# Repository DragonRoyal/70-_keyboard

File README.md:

# 70% keyboard

A low profile sleek 70% keyboard.

## Features
- **Hot Swappable**: Swap existing switches easily without needing to solder
- **LED**: Supports independently controlled RGB backlighting for each switch
- **Multi-Layered**: Work between multiple different layers for increased macros and switch options
- **TFT Screen**: A powerful and sharp TFT display 
- **Raspberry Pi**: Fast and dynamic microcontroller allowing for easy software customization
- **Rotary Encoder**: Easy to use knob for changing granular control such as volume, brightness etc

## CAD

## PCB 

> Firmware is coded in C using the QMK library

## BOM
|Type                         |Qty|Value                       |Exclude from BOM|Exclude from Board|Footprint                                                    |Price (with tax)|links                                                                                                                                                                                                                                                                                                                                                                                                                                                                                                                                            |
|-----------------------------|---|----------------------------|----------------|------------------|-------------------------------------------------------------|----------------|-------------------------------------------------------------------------------------------------------------------------------------------------------------------------------------------------------------------------------------------------------------------------------------------------------------------------------------------------------------------------------------------------------------------------------------------------------------------------------------------------------------------------------------------------|
|Microcontroller              |1  |RaspberryPi_Pico            |FALSE           |FALSE             |Module:RaspberryPi_Pico_Common_Unspecified                   |$4              | self-sourced                                                                                                                                                                                                                                                                                                                                                                                                                                                                                                                                    |
|Diode                        |79 |Diode 14B                   |FALSE           |FALSE             |Diode_SMD:D_SOD-123                                          |$15             | https://www.amazon.com/gp/product/B089KD46P6/ref=ox_sc_act_title_8?smid=A1K2H0ANPH97NN&psc=1                                                                                                                                                                                                                                                                                                                                                                                                                                                    |
|Led                          |78 |WS2812B                     |FALSE           |FALSE             |PCM_marbastlib-various:SK6812 Mini-E Leds                    |$6              | self-sourced                                                                                                                                                                                                                                                                                                                                                                                                                                                                                                                                    |
|Rotary Encoder               |1  |EC11 Rotary Encoder         |FALSE           |FALSE             |Rotary_Encoder:RotaryEncoder_Alps_EC11E-Switch_Vertical_H20mm|$3              | self sourced                                                                                                                                                                                                                                                                                                                                                                                                                                                                                                                                    |
|Switch                       |78 |Gateroen banana low profile |FALSE           |FALSE             |PCM_marbastlib-xp-gateron_lp:SW_KS33_HS_KS-2P02B01-02_HS_1u  |$35             | self sourced                                                                                                                                                                                                                                                                                                                                                                                                                                                                                                                                    |
|Screen                       |1  |1.47in TFT screen           |TRUE            |FALSE             |PCM_marbastlib-various:1.47IN TFT_SCREEN                     | 7              | self sourced                                                                                                                                                                                                                                                                                                                                                                                                                                                                                                                                    |
|Level Converter              |1  |3.3V 5V Level Shifter       |FALSE           |FALSE             |PCM_marbastlib-various:level_shifter                         |7               | self sourced                                                                                                                                                                                                                                                                                                                                                                                                                                                                                                                                    |
|3D printed parts (plate+case)|1  |PLA filament 500g           |TRUE            |FALSE             |None                                                         | 10             | self sourced                                                                                                                                                                                                                                                                                                                                                                                                                                                                                                                                    |
|Key Caps                     |78 |Key Cap set                 |TRUE            |TRUE              |NONE                                                         | 13             | https://www.amazon.com/GMKWTL-Keyboard-Compatiability-Mechanical-Keyboard/dp/B0DHZSBBGN/ref=sr_1_10?crid=Q8QKCUUYPY36&dib=eyJ2IjoiMSJ9.fwrs3L7kzoYC9Lyi1R3ookXQWckNlki_qPy9XYsRL8eoixaPVOBcJbsZt-iwJnTJds7WBFu0eCcz7btfrjkPINBELr45fnBbDHA4z57k4MjwkxalkegLYI5fEKua1gpFN4hqXenK0UHtjBB1nRiui-55GRccuGOSDW5j42Px5hd2BBhLpY2dmSPZnt28AmRuuPHAs3Wn1phLvo0gcR4tVQwwtv983OjqboYfD7py36w.qD3godhpSDs_aP7pM0q0AIdArKnzhV_a1bjScBHYfi8&dib_tag=se&keywords=keycaps%2Blow%2Bprofile&qid=1775969569&sprefix=keycaps%2Blow%2Bprofi%2Caps%2C273&sr=8-10&th=1|
|Hot Swap pieces              |78 |Pieces to enable hotswapping|FALSE           |FALSE             |None                                                         |$13             | https://www.amazon.com/DUROCK-Mechanical-Keyboard-Switches-Hot-Swap/dp/B0B4W9YMGM/ref=sr_1_2?crid=35CHQWRUJA015&dib=eyJ2IjoiMSJ9.JKoXkJJJrIVA4JnSSkGnStBHXR4IGGxla1AKDvP5V3XXNLep92NdhsBql2ii68qiNB_c7g-ZFRZQXi7_jpkLV9qVnHxPqgLZuBjQyTdpZ7GRyz4oyQSZOJoVgddlCynht3oA2-7a3M9IHi13k7zsOeL7wTkQXblP_iKm-qXsR8phlb-2kgSF3aj1uBRLhr7IE7VCK2ORV3m670alLx6cIYPoHnYoNUGfPmrVBh7ICmw.oYdHgUtbILh2GUhhMcQZcBHLQ_plr3crWkFkTJia-B8&dib_tag=se&keywords=hotswap&qid=1775969494&sprefix=hotswa%2Caps%2C238&sr=8-2                                           |
|PCB Board                    |1  |Pcb from JLCPCB             |FALSE           |FALSE             |                                                             |$35             | https://jlcpcb.com/                                                                                                                                                                                                                                                                                                                                                                                                                                                                                                                             |

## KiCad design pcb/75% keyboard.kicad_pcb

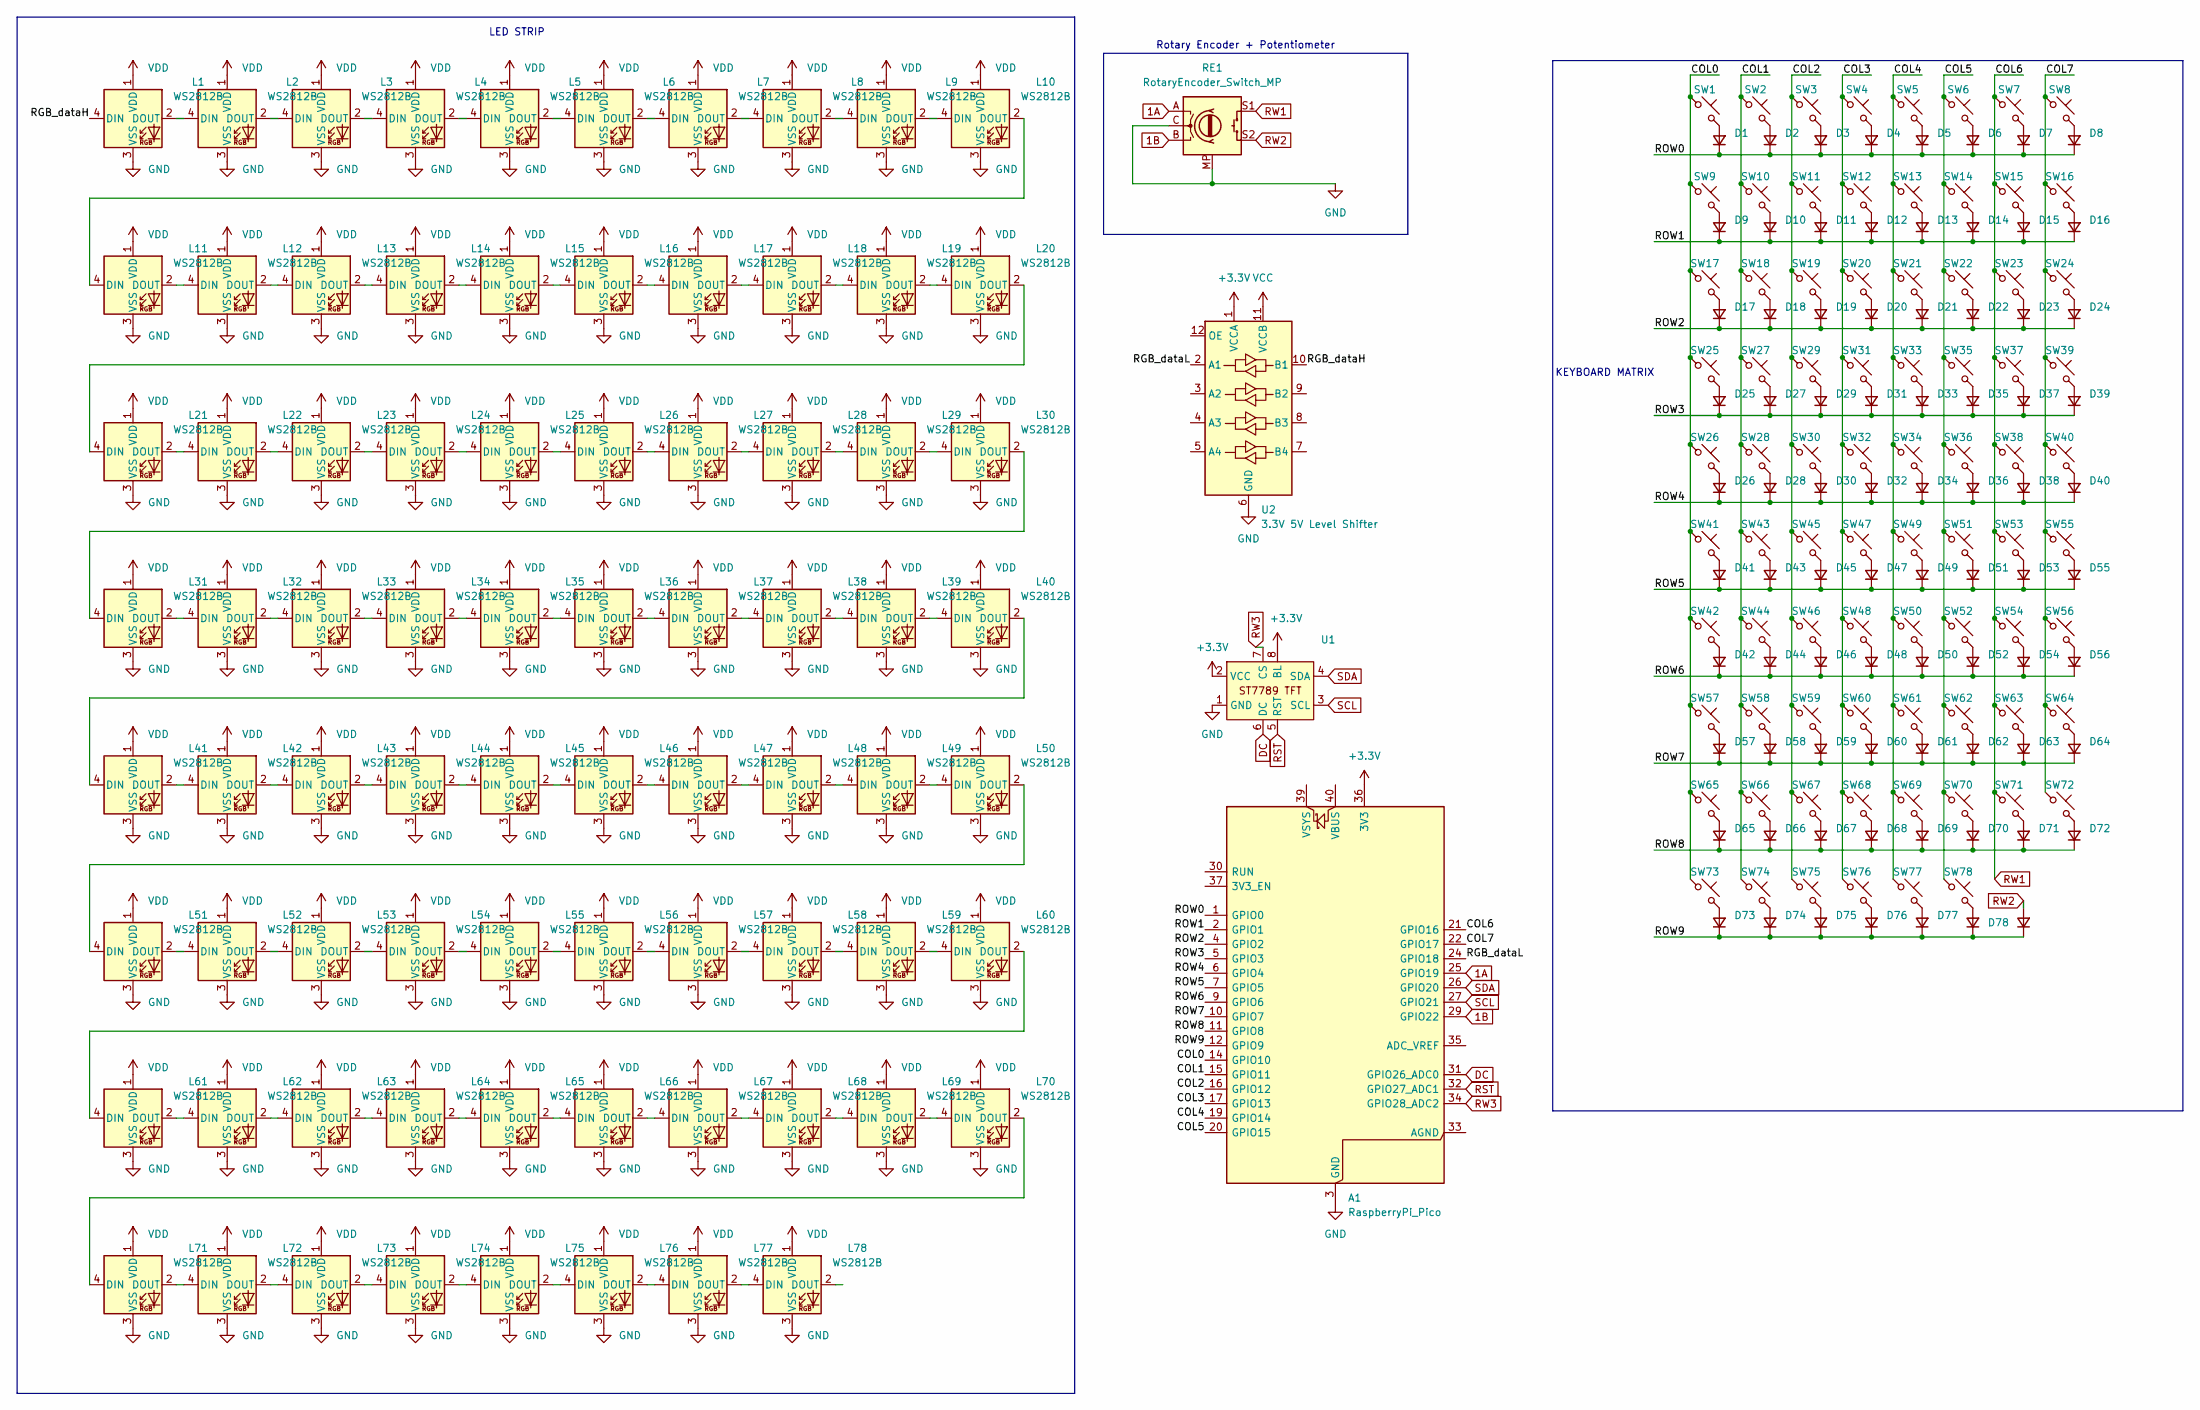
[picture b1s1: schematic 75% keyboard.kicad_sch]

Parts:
A1: RaspberryPi_Pico; RaspberryPi_Pico_Common_Unspecified
D1, D2, D3, D4, D5, D6, D7, D8, D9, D10, D11, D12, D13, D14, D15, D16, D17, D18, D19, D20, D21, D22, D23, D24, D25, D26, D27, D28, D29, D30, D31, D32, D33, D34, D35, D36, D37, D38, D39, D40, D41, D42, D43, D44, D45, D46, D47, D48, D49, D50, D51, D52, D53, D54, D55, D56, D57, D58, D59, D60, D61, D62, D63, D64, D65, D66, D67, D68, D69, D70, D71, D72, D73, D74, D75, D76, D77, D78, D79: D_Small; D_SOD-123
L1, L2, L3, L4, L5, L6, L7, L8, L9, L10, L11, L12, L13, L14, L15, L16, L17, L18, L19, L20, L21, L22, L23, L24, L25, L26, L27, L28, L29, L30, L31, L32, L33, L34, L35, L36, L37, L38, L39, L40, L41, L42, L43, L44, L45, L46, L47, L48, L49, L50, L51, L52, L53, L54, L55, L56, L57, L58, L59, L60, L61, L62, L63, L64, L65, L66, L67, L68, L69, L70, L71, L72, L73, L74, L75, L76, L77, L78: WS2812B; SK6812 Mini-E Leds
RE1: RotaryEncoder_Switch_MP; RotaryEncoder_Alps_EC11E-Switch_Vertical_H20mm
SW1, SW2, SW3, SW4, SW5, SW6, SW7, SW8, SW9, SW10, SW11, SW12, SW13, SW14, SW15, SW16, SW17, SW18, SW19, SW20, SW21, SW22, SW23, SW24, SW25, SW26, SW27, SW28, SW29, SW30, SW31, SW32, SW33, SW34, SW35, SW36, SW37, SW38, SW39, SW40, SW41, SW42, SW43, SW44, SW45, SW46, SW47, SW48, SW49, SW50, SW51, SW52, SW53, SW54, SW55, SW56, SW57, SW58, SW59, SW60, SW61, SW62, SW63, SW64, SW65, SW66, SW67, SW68, SW69, SW70, SW71, SW72, SW73, SW74, SW75, SW76, SW77, SW78: SW_Push_45deg; SW_KS33_HS_KS-2P02B01-02_HS_1u
U1: 1.47IN TFT_SCREEN
U2: 3.3V 5V Level Shifter; level_shifter

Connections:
1A: A1.25 (GPIO19), RE1.A
1B: A1.29 (GPIO22), RE1.B
+3.3V: A1.36 (3V3), U1.2 (VCC), U1.8 (BL), U2.1 (VCCA); also elsewhere on the board
/COL0: A1.14 (GPIO10), SW1.1, SW9.1, SW17.1, SW25.1, SW26.1, SW41.1, SW42.1, SW57.1, SW65.1, SW73.1
/COL1: A1.15 (GPIO11), SW2.1, SW10.1, SW18.1, SW27.1, SW28.1, SW43.1, SW44.1, SW58.1, SW66.1, SW74.1
/COL2: A1.16 (GPIO12), SW3.1, SW11.1, SW19.1, SW29.1, SW30.1, SW45.1, SW46.1, SW59.1, SW67.1, SW75.1
/COL3: A1.17 (GPIO13), SW4.1, SW12.1, SW20.1, SW31.1, SW32.1, SW47.1, SW48.1, SW60.1, SW68.1, SW76.1
/COL4: A1.19 (GPIO14), SW5.1, SW13.1, SW21.1, SW33.1, SW34.1, SW49.1, SW50.1, SW61.1, SW69.1, SW77.1
/COL5: A1.20 (GPIO15), SW6.1, SW14.1, SW22.1, SW35.1, SW36.1, SW51.1, SW52.1, SW62.1, SW70.1, SW78.1
/COL7: A1.22 (GPIO17), SW8.1, SW16.1, SW24.1, SW39.1, SW40.1, SW55.1, SW56.1, SW64.1, SW72.1
/RGB_dataH: L1.4 (DIN), U2.10 (B1)
/RGB_dataL: A1.24 (GPIO18), U2.2 (A1)
/ROW0: A1.1 (GPIO0), D1.1 (K), D2.1 (K), D3.1 (K), D4.1 (K), D5.1 (K), D6.1 (K), D7.1 (K), D8.1 (K)
/ROW1: A1.2 (GPIO1), D9.1 (K), D10.1 (K), D11.1 (K), D12.1 (K), D13.1 (K), D14.1 (K), D15.1 (K), D16.1 (K)
/ROW2: A1.4 (GPIO2), D17.1 (K), D18.1 (K), D19.1 (K), D20.1 (K), D21.1 (K), D22.1 (K), D23.1 (K), D24.1 (K)
/ROW3: A1.5 (GPIO3), D25.1 (K), D27.1 (K), D29.1 (K), D31.1 (K), D33.1 (K), D35.1 (K), D37.1 (K), D39.1 (K)
/ROW4: A1.6 (GPIO4), D26.1 (K), D28.1 (K), D30.1 (K), D32.1 (K), D34.1 (K), D36.1 (K), D38.1 (K), D40.1 (K)
/ROW5: A1.7 (GPIO5), D41.1 (K), D43.1 (K), D45.1 (K), D47.1 (K), D49.1 (K), D51.1 (K), D53.1 (K), D55.1 (K)
/ROW6: A1.9 (GPIO6), D42.1 (K), D44.1 (K), D46.1 (K), D48.1 (K), D50.1 (K), D52.1 (K), D54.1 (K), D56.1 (K)
/ROW7: A1.10 (GPIO7), D57.1 (K), D58.1 (K), D59.1 (K), D60.1 (K), D61.1 (K), D62.1 (K), D63.1 (K), D64.1 (K)
/ROW8: A1.11 (GPIO8), D65.1 (K), D66.1 (K), D67.1 (K), D68.1 (K), D69.1 (K), D70.1 (K), D71.1 (K), D72.1 (K)
/ROW9: A1.12 (GPIO9), D73.1 (K), D74.1 (K), D75.1 (K), D76.1 (K), D77.1 (K), D78.1 (K), D79.1 (K)
DC: A1.31 (GPIO26_ADC0), U1.6 (DC)
GND: A1.3 (GND), A1.8 (GND), A1.13 (GND), A1.18 (GND), A1.23 (GND), A1.28 (GND), A1.38 (GND), L1.3 (VSS), L2.3 (VSS), L3.3 (VSS), L4.3 (VSS), L5.3 (VSS), L6.3 (VSS), L7.3 (VSS), L8.3 (VSS), L9.3 (VSS), L10.3 (VSS), L11.3 (VSS), L12.3 (VSS), L13.3 (VSS), L14.3 (VSS), L15.3 (VSS), L16.3 (VSS), L17.3 (VSS), L18.3 (VSS), L19.3 (VSS), L20.3 (VSS), L21.3 (VSS), L22.3 (VSS), L23.3 (VSS), L24.3 (VSS), L25.3 (VSS), L26.3 (VSS), L27.3 (VSS), L28.3 (VSS), L29.3 (VSS), L30.3 (VSS), L31.3 (VSS), L32.3 (VSS), L33.3 (VSS), L34.3 (VSS), L35.3 (VSS), L36.3 (VSS), L37.3 (VSS), L38.3 (VSS), L39.3 (VSS), L40.3 (VSS), L41.3 (VSS), L42.3 (VSS), L43.3 (VSS), L44.3 (VSS), L45.3 (VSS), L46.3 (VSS), L47.3 (VSS), L48.3 (VSS), L49.3 (VSS), L50.3 (VSS), L51.3 (VSS), L52.3 (VSS), L53.3 (VSS), L54.3 (VSS), L55.3 (VSS), L56.3 (VSS), L57.3 (VSS), L58.3 (VSS), L59.3 (VSS), L60.3 (VSS), L61.3 (VSS), L62.3 (VSS), L63.3 (VSS), L64.3 (VSS), L65.3 (VSS), L66.3 (VSS), L67.3 (VSS), L68.3 (VSS), L69.3 (VSS), L70.3 (VSS), L71.3 (VSS), L72.3 (VSS), L73.3 (VSS), L74.3 (VSS), L75.3 (VSS), L76.3 (VSS), L77.3 (VSS), L78.3 (VSS), RE1.C, RE1.MP, U1.1 (GND), U2.6 (GND); also elsewhere on the board
unnamed: D1.2 (A), SW1.2
unnamed: D2.2 (A), SW2.2
unnamed: D3.2 (A), SW3.2
unnamed: D4.2 (A), SW4.2
unnamed: D5.2 (A), SW5.2
unnamed: D6.2 (A), SW6.2
unnamed: D7.2 (A), SW7.2
unnamed: D8.2 (A), SW8.2
unnamed: D9.2 (A), SW9.2
unnamed: D10.2 (A), SW10.2
unnamed: D11.2 (A), SW11.2
unnamed: D12.2 (A), SW12.2
unnamed: D13.2 (A), SW13.2
unnamed: D14.2 (A), SW14.2
unnamed: D15.2 (A), SW15.2
unnamed: D16.2 (A), SW16.2
unnamed: D17.2 (A), SW17.2
unnamed: D18.2 (A), SW18.2
unnamed: D19.2 (A), SW19.2
unnamed: D20.2 (A), SW20.2
unnamed: D21.2 (A), SW21.2
unnamed: D22.2 (A), SW22.2
unnamed: D23.2 (A), SW23.2
unnamed: D24.2 (A), SW24.2
unnamed: D25.2 (A), SW25.2
unnamed: D26.2 (A), SW26.2
unnamed: D27.2 (A), SW27.2
unnamed: D28.2 (A), SW28.2
unnamed: D29.2 (A), SW29.2
unnamed: D30.2 (A), SW30.2
unnamed: D31.2 (A), SW31.2
unnamed: D32.2 (A), SW32.2
unnamed: D33.2 (A), SW33.2
unnamed: D34.2 (A), SW34.2
unnamed: D35.2 (A), SW35.2
unnamed: D36.2 (A), SW36.2
unnamed: D37.2 (A), SW37.2
unnamed: D38.2 (A), SW38.2
unnamed: D39.2 (A), SW39.2
unnamed: D40.2 (A), SW40.2
unnamed: D41.2 (A), SW41.2
unnamed: D42.2 (A), SW42.2
unnamed: D43.2 (A), SW43.2
unnamed: D44.2 (A), SW44.2
unnamed: D45.2 (A), SW45.2
unnamed: D46.2 (A), SW46.2
unnamed: D47.2 (A), SW47.2
unnamed: D48.2 (A), SW48.2
unnamed: D49.2 (A), SW49.2
unnamed: D50.2 (A), SW50.2
unnamed: D51.2 (A), SW51.2
unnamed: D52.2 (A), SW52.2
unnamed: D53.2 (A), SW53.2
unnamed: D54.2 (A), SW54.2
unnamed: D55.2 (A), SW55.2
unnamed: D56.2 (A), SW56.2
unnamed: D57.2 (A), SW57.2
unnamed: D58.2 (A), SW58.2
unnamed: D59.2 (A), SW59.2
unnamed: D60.2 (A), SW60.2
unnamed: D61.2 (A), SW61.2
unnamed: D62.2 (A), SW62.2
unnamed: D63.2 (A), SW63.2
unnamed: D64.2 (A), SW64.2
unnamed: D65.2 (A), SW65.2
unnamed: D66.2 (A), SW66.2
unnamed: D67.2 (A), SW67.2
unnamed: D68.2 (A), SW68.2
unnamed: D69.2 (A), SW69.2
unnamed: D70.2 (A), SW70.2
unnamed: D71.2 (A), SW71.2
unnamed: D72.2 (A), SW72.2
unnamed: D73.2 (A), SW73.2
unnamed: D74.2 (A), SW74.2
unnamed: D75.2 (A), SW75.2
unnamed: D76.2 (A), SW76.2
unnamed: D77.2 (A), SW77.2
unnamed: D78.2 (A), SW78.2
unnamed: L1.2 (DOUT), L2.4 (DIN)
unnamed: L2.2 (DOUT), L3.4 (DIN)
unnamed: L3.2 (DOUT), L4.4 (DIN)
unnamed: L4.2 (DOUT), L5.4 (DIN)
unnamed: L5.2 (DOUT), L6.4 (DIN)
unnamed: L6.2 (DOUT), L7.4 (DIN)
unnamed: L7.2 (DOUT), L8.4 (DIN)
unnamed: L8.2 (DOUT), L9.4 (DIN)
unnamed: L9.2 (DOUT), L10.4 (DIN)
unnamed: L10.2 (DOUT), L11.4 (DIN)
unnamed: L11.2 (DOUT), L12.4 (DIN)
unnamed: L12.2 (DOUT), L13.4 (DIN)
unnamed: L13.2 (DOUT), L14.4 (DIN)
unnamed: L14.2 (DOUT), L15.4 (DIN)
unnamed: L15.2 (DOUT), L16.4 (DIN)
unnamed: L16.2 (DOUT), L17.4 (DIN)
unnamed: L17.2 (DOUT), L18.4 (DIN)
unnamed: L18.2 (DOUT), L19.4 (DIN)
unnamed: L19.2 (DOUT), L20.4 (DIN)
unnamed: L20.2 (DOUT), L21.4 (DIN)
unnamed: L21.2 (DOUT), L22.4 (DIN)
unnamed: L22.2 (DOUT), L23.4 (DIN)
unnamed: L23.2 (DOUT), L24.4 (DIN)
unnamed: L24.2 (DOUT), L25.4 (DIN)
unnamed: L25.2 (DOUT), L26.4 (DIN)
unnamed: L26.2 (DOUT), L27.4 (DIN)
unnamed: L27.2 (DOUT), L28.4 (DIN)
unnamed: L28.2 (DOUT), L29.4 (DIN)
unnamed: L29.2 (DOUT), L30.4 (DIN)
unnamed: L30.2 (DOUT), L31.4 (DIN)
unnamed: L31.2 (DOUT), L32.4 (DIN)
unnamed: L32.2 (DOUT), L33.4 (DIN)
unnamed: L33.2 (DOUT), L34.4 (DIN)
unnamed: L34.2 (DOUT), L35.4 (DIN)
unnamed: L35.2 (DOUT), L36.4 (DIN)
unnamed: L36.2 (DOUT), L37.4 (DIN)
unnamed: L37.2 (DOUT), L38.4 (DIN)
unnamed: L38.2 (DOUT), L39.4 (DIN)
unnamed: L39.2 (DOUT), L40.4 (DIN)
unnamed: L40.2 (DOUT), L41.4 (DIN)
unnamed: L41.2 (DOUT), L42.4 (DIN)
unnamed: L42.2 (DOUT), L43.4 (DIN)
unnamed: L43.2 (DOUT), L44.4 (DIN)
unnamed: L44.2 (DOUT), L45.4 (DIN)
unnamed: L45.2 (DOUT), L46.4 (DIN)
unnamed: L46.2 (DOUT), L47.4 (DIN)
unnamed: L47.2 (DOUT), L48.4 (DIN)
unnamed: L48.2 (DOUT), L49.4 (DIN)
unnamed: L49.2 (DOUT), L50.4 (DIN)
unnamed: L50.2 (DOUT), L51.4 (DIN)
unnamed: L51.2 (DOUT), L52.4 (DIN)
unnamed: L52.2 (DOUT), L53.4 (DIN)
unnamed: L53.2 (DOUT), L54.4 (DIN)
unnamed: L54.2 (DOUT), L55.4 (DIN)
unnamed: L55.2 (DOUT), L56.4 (DIN)
unnamed: L56.2 (DOUT), L57.4 (DIN)
unnamed: L57.2 (DOUT), L58.4 (DIN)
unnamed: L58.2 (DOUT), L59.4 (DIN)
unnamed: L59.2 (DOUT), L60.4 (DIN)
unnamed: L60.2 (DOUT), L61.4 (DIN)
unnamed: L61.2 (DOUT), L62.4 (DIN)
unnamed: L62.2 (DOUT), L63.4 (DIN)
unnamed: L63.2 (DOUT), L64.4 (DIN)
unnamed: L64.2 (DOUT), L65.4 (DIN)
unnamed: L65.2 (DOUT), L66.4 (DIN)
unnamed: L66.2 (DOUT), L67.4 (DIN)
unnamed: L67.2 (DOUT), L68.4 (DIN)
unnamed: L68.2 (DOUT), L69.4 (DIN)
unnamed: L69.2 (DOUT), L70.4 (DIN)
unnamed: L70.2 (DOUT), L71.4 (DIN)
unnamed: L71.2 (DOUT), L72.4 (DIN)
unnamed: L72.2 (DOUT), L73.4 (DIN)
unnamed: L73.2 (DOUT), L74.4 (DIN)
unnamed: L74.2 (DOUT), L75.4 (DIN)
unnamed: L75.2 (DOUT), L76.4 (DIN)
unnamed: L76.2 (DOUT), L77.4 (DIN)
unnamed: L77.2 (DOUT), L78.4 (DIN)
RST: A1.32 (GPIO27_ADC1), U1.5 (RST)
RW1: A1.21 (GPIO16), RE1.S1, SW7.1, SW15.1, SW23.1, SW37.1, SW38.1, SW53.1, SW54.1, SW63.1, SW71.1
RW2: D79.2 (A), RE1.S2
RW3: A1.34 (GPIO28_ADC2), U1.7 (CS); also elsewhere on the board
SCL: A1.27 (GPIO21), U1.3 (SCL)
SDA: A1.26 (GPIO20), U1.4 (SDA)
VCC: U2.11 (VCCB)
VDD: L1.1 (VDD), L2.1 (VDD), L3.1 (VDD), L4.1 (VDD), L5.1 (VDD), L6.1 (VDD), L7.1 (VDD), L8.1 (VDD), L9.1 (VDD), L10.1 (VDD), L11.1 (VDD), L12.1 (VDD), L13.1 (VDD), L14.1 (VDD), L15.1 (VDD), L16.1 (VDD), L17.1 (VDD), L18.1 (VDD), L19.1 (VDD), L20.1 (VDD), L21.1 (VDD), L22.1 (VDD), L23.1 (VDD), L24.1 (VDD), L25.1 (VDD), L26.1 (VDD), L27.1 (VDD), L28.1 (VDD), L29.1 (VDD), L30.1 (VDD), L31.1 (VDD), L32.1 (VDD), L33.1 (VDD), L34.1 (VDD), L35.1 (VDD), L36.1 (VDD), L37.1 (VDD), L38.1 (VDD), L39.1 (VDD), L40.1 (VDD), L41.1 (VDD), L42.1 (VDD), L43.1 (VDD), L44.1 (VDD), L45.1 (VDD), L46.1 (VDD), L47.1 (VDD), L48.1 (VDD), L49.1 (VDD), L50.1 (VDD), L51.1 (VDD), L52.1 (VDD), L53.1 (VDD), L54.1 (VDD), L55.1 (VDD), L56.1 (VDD), L57.1 (VDD), L58.1 (VDD), L59.1 (VDD), L60.1 (VDD), L61.1 (VDD), L62.1 (VDD), L63.1 (VDD), L64.1 (VDD), L65.1 (VDD), L66.1 (VDD), L67.1 (VDD), L68.1 (VDD), L69.1 (VDD), L70.1 (VDD), L71.1 (VDD), L72.1 (VDD), L73.1 (VDD), L74.1 (VDD), L75.1 (VDD), L76.1 (VDD), L77.1 (VDD), L78.1 (VDD)

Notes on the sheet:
LED STRIP
Rotary Encoder + Potentiometer
KEYBOARD MATRIX

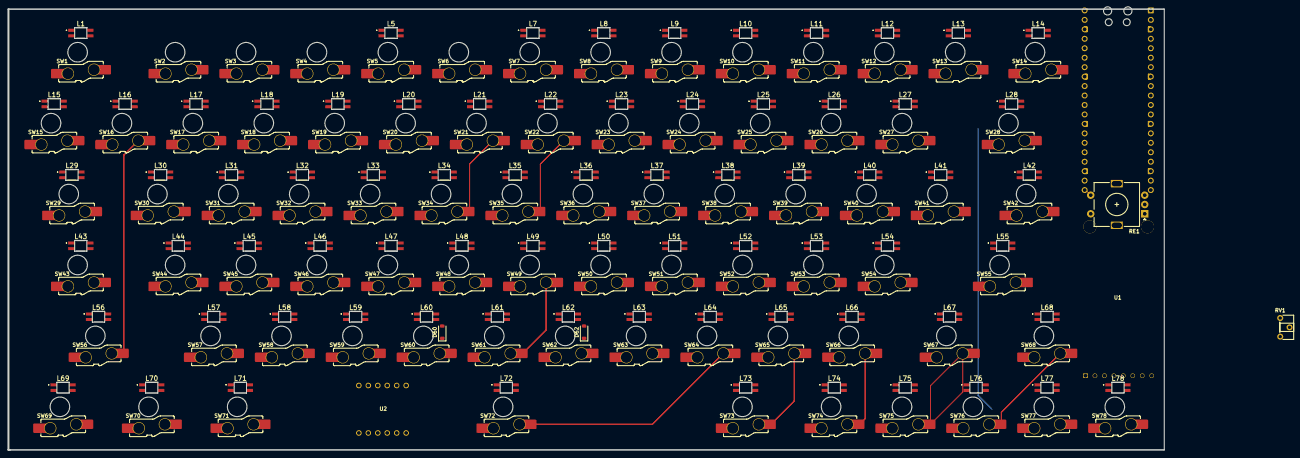
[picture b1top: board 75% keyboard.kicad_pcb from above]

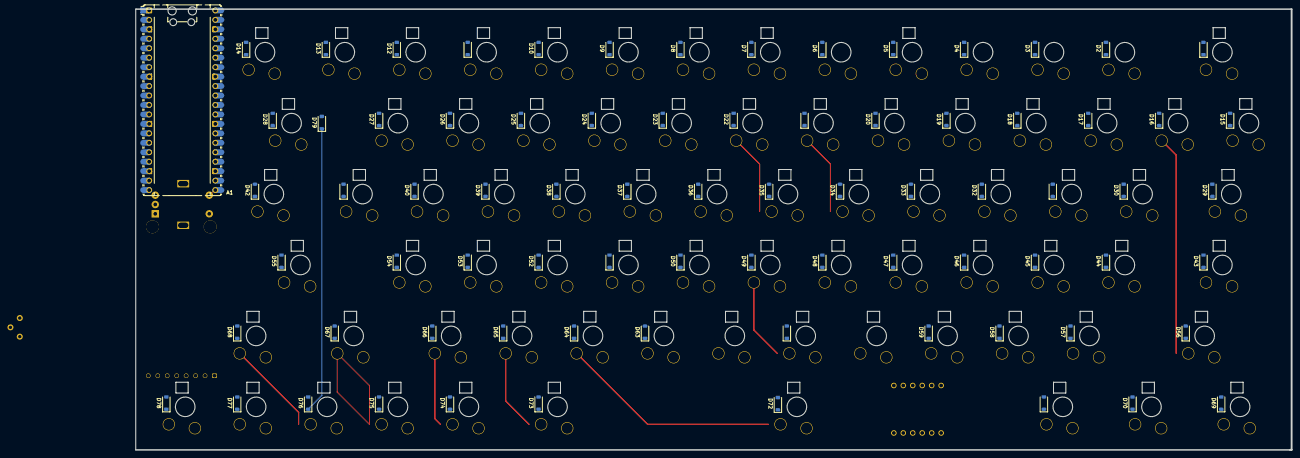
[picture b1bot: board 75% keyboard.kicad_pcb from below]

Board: 2 copper layers, 310.5 x 118.4 mm, 236 parts (78 on the bottom side), 180 nets.

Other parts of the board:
RV1: R_Potentiometer; Potentiometer_ACP_CA6-H2,5_Horizontal

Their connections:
+3.3V: RV1.1; also elsewhere on the board
GND: RV1.3; also elsewhere on the board
RW3: RV1.2; also elsewhere on the board

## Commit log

2025-12-26 Create firmware
2025-12-26 Update README with CAD and PCB images
    Added multiple images to the CAD and PCB sections of the README.
2025-12-27 updates bom
2026-04-29 production files added
2026-05-01 Update BOM with additional components and details
    Added new components including microcontroller, diodes, LEDs, rotary encoder, and more to the BOM.
2026-05-01 Add new BOM image to README
2026-05-02 Fix formatting and sourcing in keyboard BOM
    Added a comma at the end of the Microcontroller line and corrected the sourcing text for Rotary Encoder and Switch.
2026-05-02 Create solid
2026-05-02 Rename 75_assem.zip to 70_assem.zip
